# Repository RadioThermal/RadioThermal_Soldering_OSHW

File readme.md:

RadioThermal 470KHz Induction Soldering Station - Open Source Hardware
========================

This repository contains the designs and resources to build a high-performance induction soldering iron at a relatively low cost. [Check out radiothermal.com for more information.](https://radiothermal.com/products.html)

### [Join our Discord server](https://discord.gg/hySrP3z9Kq)

### [Join our mailing list to get updates on this project](https://radiothermal.com/mailing.html)

The 470KHz soldering system is made up of four major components: the power supply, the handpiece, the cable, and the workstand. Follow the links to see the assembly instructions and files for each component.

### [Power Supply](https://github.com/RadioThermal/RadioThermal_Soldering_OSHW/tree/main/Power%20Supply)

The power supply is the core of the 470KHz system. It consists of a PCB design that includes a class-E amplifier and contains impedance matching circuitry to properly provide power to the soldering iron tip. 

### [Handpiece](https://github.com/RadioThermal/RadioThermal_Soldering_OSHW/tree/main/Handpiece)

The handpiece is the primary user interface of the soldering system. It consists of a core built with brass tubing and an outer 3D printed grip for comfort during use.

### [Cable](https://github.com/RadioThermal/RadioThermal_Soldering_OSHW/tree/main/Cable)

The cable is a specially modified RG-174 coaxial cable with SMA connectors on each end. A silicone jacket has been added for burn resistance, with additional silicone layers on each end for improved strain relief

### [Workstand](https://github.com/RadioThermal/RadioThermal_Soldering_OSHW/tree/main/Workstand)

The workstand is a primarly 3D printed part that gives the user a safe place to their hot soldering iron, along with brass wool to clean the tip. Magnets are used to cool down the soldering iron tip when not in use. The back of the stand contains storage for four tips.

### [Extra - Compatibility Adapters](https://github.com/RadioThermal/RadioThermal_Soldering_OSHW/tree/main/Adapters)

We have designed compatibility adapters to allow our cable and handpiece to be used with preexisting 470KHz power supplies including Metcal PS, Metcal MFR, and Thermaltronics TMT-2000.

# Project Status

Here is an overview of the current state of completion for each major component of the project

| Component              | Status                      |
| ---------------------- | --------------------------- |
| Power Supply           | Updated to V2.5B            |
| Handpiece              | Complete                    |
| Cable                  | Complete                    |
| Workstand              | Complete                    |
| Compatibility Adapters | Updated version coming soon |

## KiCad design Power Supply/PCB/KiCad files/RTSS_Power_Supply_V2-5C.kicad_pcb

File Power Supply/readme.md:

# Power Supply

The power supply is the core of the 470KHz system. It is based upon a class-E amplifier and contains impedance matching circuitry to properly provide power to the soldering iron tip.

#### The PCB

The provided PCB design includes all basic functionality needed to operate a 470KHz soldering iron tip. 

The design includes provisions for inrush current limiting, reverse polarity protection, a cooling fan, and two different types of oscillators. The inductors, apart from the fixed 33uH inductor, are all based around the [Kool Mu 0077932A7 core](https://www.mag-inc.com/Media/Magnetics/Datasheets/0077932A7.pdf), which is currently only available from Digikey, though we are looking for alternatives. 

In version 2.5B of the PCB, we have made a few improvements to reduce cost and increase reliability compared with version 2.3B1. Most notably the oscillator section has been redesigned to eliminate the need for a microcontroller and now only relies on a 7.6MHz crystal oscillator and TTL logic. To reduce costs, we have eliminated the daughter board by moving everything onto the main board, additionally L2 has been updated to only use a single inductor core from the two cores required on previous versions. Moving all of this new hardware onto the main board has had the consequence of causing us to remove the TO-247 MOSFET option in favor of TO-220 to save space. 

In the version 2.5C release, the reference designators have been updated on most components to better reflect their placement within the design.

Components required to assemble the board can be found in the [Digikey list we maintain](https://www.digikey.com/en/mylists/list/9TG6QR7M1O) , please let us know if there is a stocking issue for a component so that we can find a suitable alternative.

**Special note:** if you are one of the few people with a **V2.5** non-B PCB, please replace the 74LVC1G14 with a [74LVC2G14](https://www.digikey.com/en/products/detail/evvo/SN74LVC2G14DBVR-EV/22674516) and ensure the [74LVC1GU04](https://www.digikey.com/en/products/detail/texas-instruments/SN74LVC1GU04DBVR/377459) is a SOT23-5 package

#### External DC Power Supplies

For testing we have been using Chicony A15-180P1A 20V 180W power supplies, however any power supply in the 18-24V range with a 100W or higher rating will work. We recommend utilizing a laptop power supply since they can be found on the used market at reasonable prices. Alternatively, a USB-C PD trigger board can be used in conjunction with a USB PD power supply that supports 20V 5A output.

#### The Case

The case design adds additional functionality to the PCB including a barrel jack for power input, a convenient power switch, power indicator LED, cooling fan, and a ground connection point. The airflow paths of the case have been optimized to exhaust out the front and back with the intake on top, keeping all of the inductors cool.

The electronics parts and fasteners for the case [can be purchased from Digikey](https://www.digikey.com/en/mylists/list/JW0L0CD7FY). 

The case fan mounts are only designed to support Delta AFB0712 series fans at present, other 70mm fans can be used by removing the fan mounting posts and gluing the four corners of the fan in place.

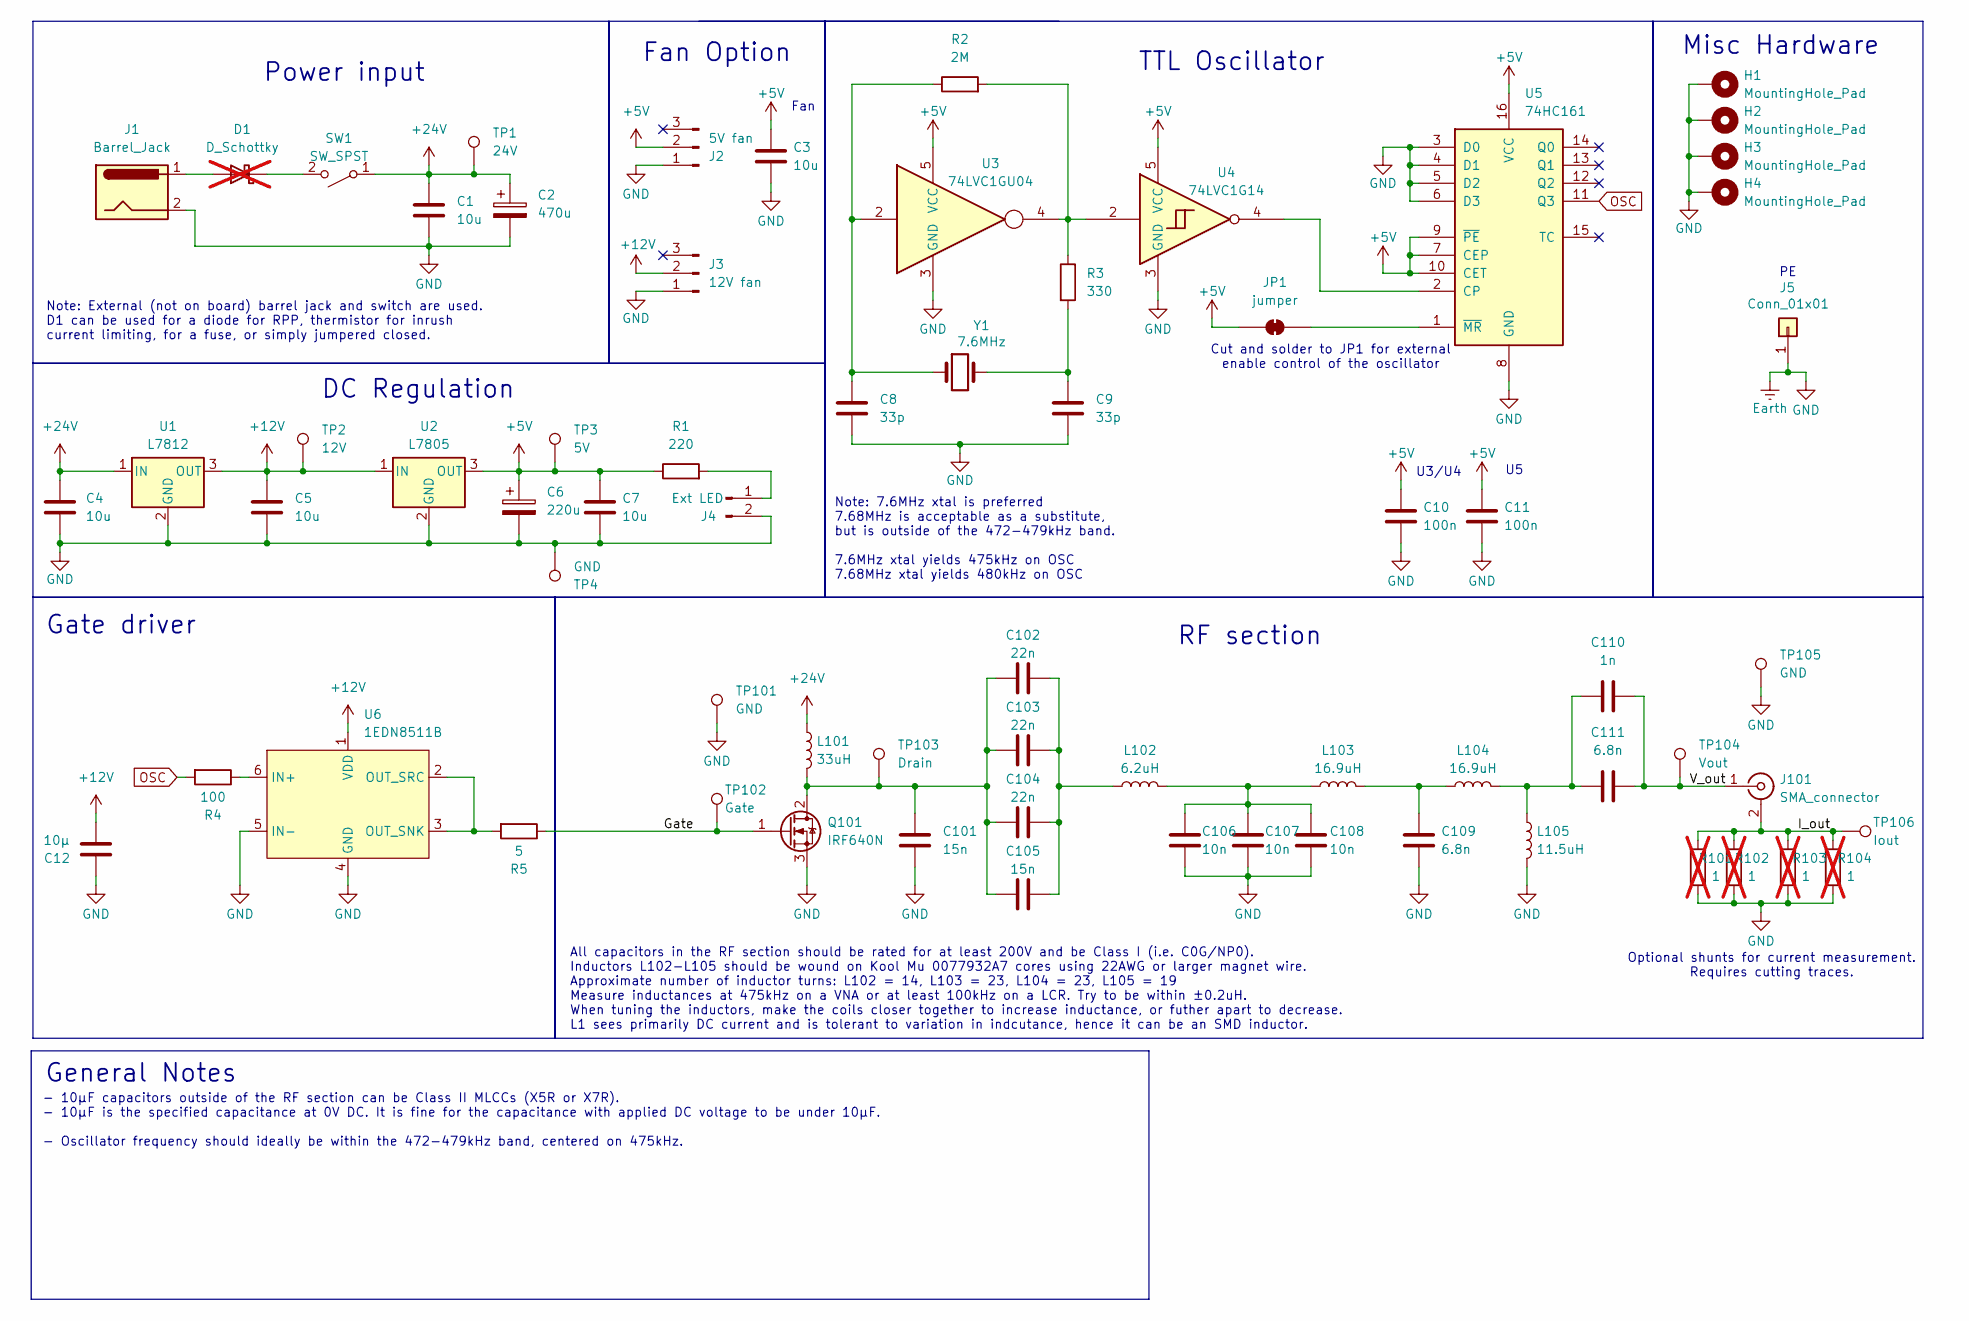
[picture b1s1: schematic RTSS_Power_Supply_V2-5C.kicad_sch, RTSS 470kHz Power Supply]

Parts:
C1, C3, C4, C5, C7: 10u; C_1206_3216Metric_Pad1.33x1.80mm_HandSolder
C2: 470u; CP_Radial_D10.0mm_P5.00mm_P7.50mm
C6: 220u; CP_Radial_D6.3mm_P2.50mm
C8, C9: 33p; C_0603_1608Metric
C10, C11: 100n; C_0603_1608Metric
C12: 10µ; C_1206_3216Metric_Pad1.33x1.80mm_HandSolder
C101, C105: 15n; C_1210_3225Metric_Pad1.33x2.70mm_HandSolder
C102, C103, C104: 22n; C_1206_3216Metric_Pad1.33x1.80mm_HandSolder
C106, C107, C108: 10n; C_1206_3216Metric_Pad1.33x1.80mm_HandSolder
C109, C111: 6.8n; C_1210_3225Metric_Pad1.33x2.70mm_HandSolder
C110: 1n; C_1206_3216Metric_Pad1.33x1.80mm_HandSolder
D1: D_Schottky; TO-220-2_Vertical; not fitted
H1, H2, H3, H4: MountingHole_Pad; MountingHole_3.2mm_M3_DIN965_Pad
J1: Barrel_Jack; 3D-JWT_A3963_1x02_P3.96mm_Vertical
J2: 5V fan; FanPinHeader_1x03_P2.54mm_Vertical
J3: 12V fan; FanPinHeader_1x03_P2.54mm_Vertical
J4: Ext LED; PinHeader_1x02_P2.54mm_Vertical
J5: Conn_01x01; SolderWire-1sqmm_1x01_D1.4mm_OD2.7mm
J101: SMA_connector; SMA_EdgeMount_Horizontal
JP1: jumper; SolderJumper-2_P1.3mm_Bridged_RoundedPad1.0x1.5mm
L101: 33uH; L_Pulse_PA4343
L102: 6.2uH; L_Koolmu_1x_small_THTonly_0077932A7
L103, L104: 16.9uH; L_Koolmu_1x_small_THTonly_0077932A7
L105: 11.5uH; L_Koolmu_1x_small_THTonly_0077932A7
Q101: IRF640N; 3D_TO-220-3_Vertical
R1: 220; C_0805_2012Metric_Pad1.18x1.45mm_HandSolder
R2: 2M; R_0805_2012Metric
R3: 330; R_0805_2012Metric
R4: 100; R_0805_2012Metric
R5: 5; Bridge_R_0805_2012Metric
R101, R102, R103, R104: 1; Bridge_R_1206_3216Metric; not fitted
SW1: SW_SPST; 3D-JWT_A3963_1x02_P3.96mm_Vertical
TP1: 24V; TestPoint_Plated_Hole_D2.0mm
TP2: 12V; TestPoint_Pad_D1.0mm
TP3: 5V; TestPoint_Pad_D1.0mm
TP4: GND; TestPoint_Pad_D1.0mm
TP101, TP105: GND; TestPoint_THTPad_2.0x2.0mm_Drill1.0mm
TP102: Gate; TestPoint_THTPad_2.0x2.0mm_Drill1.0mm
TP103: Drain; TestPoint_THTPad_2.0x2.0mm_Drill1.0mm
TP104: Vout; TestPoint_THTPad_2.0x2.0mm_Drill1.0mm
TP106: Iout; TestPoint_THTPad_2.0x2.0mm_Drill1.0mm
U1: L7812; TO-252-3_TabPin2
U2: L7805; TO-252-3_TabPin2
U3: 74LVC1GU04; SOT-553
U4: 74LVC1G14; SOT-553
U5: 74HC161; SOP-16_4.4x10.4mm_P1.27mm
U6: 1EDN8511B; SOT-23-6_Handsoldering
Y1: 7.6MHz; Crystal_SMD_HC49-SD

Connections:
+5V: C3.1, C6.1, C7.1, C10.1, C11.1, J2.2, JP1.1 (A), R1.1, TP3.1 (1_1), U2.3 (OUT), U3.5 (VCC), U4.5 (VCC), U5.7 (CEP), U5.9 (~PE), U5.10 (CET), U5.16 (VCC)
+12V: C5.1, C12.2, J3.2, TP2.1 (1_1), U1.3 (OUT), U2.1 (IN), U6.1 (VDD)
+24V: C1.1, C2.1, C4.1, L101.1, SW1.1 (A), TP1.1 (1_1), U1.1 (IN)
/Gate: Q101.1 (G), R5.1, TP102.1 (1_1)
/I_out: J101.2 (Ext), R101.1, R102.1, R103.1, R104.1, TP106.1 (1_1)
/V_out: C110.2, C111.2, J101.1 (In), TP104.1 (1_1)
Earth: C1.2, C2.2, C3.2, C4.2, C5.2, C6.2, C7.2, C8.2, C9.2, C10.2, C11.2, C12.1, C101.2, C106.2, C107.2, C108.2, C109.2, H1.1 (1_1), H2.1 (1_1), H3.1 (1_1), H4.1 (1_1), J1.2, J2.1, J3.1, J4.2, J5.1 (Pin_1_1), L105.2, Q101.3 (S), R101.2, R102.2, R103.2, R104.2, TP4.1 (1_1), TP101.1 (1_1), TP105.1 (1_1), U1.2 (GND), U2.2 (GND), U3.3 (GND), U4.3 (GND), U5.3 (D0), U5.4 (D1), U5.5 (D2), U5.6 (D3), U5.8 (GND), U6.4 (GND), U6.5 (IN-)
unnamed: C8.1, R2.1, U3.2, Y1.1
unnamed: C9.1, R3.2, Y1.2
unnamed: C102.2, C103.2, C104.2, C105.2, L102.1
unnamed: C106.1, C107.1, C108.1, L102.2, L103.1
unnamed: C109.1, L103.2, L104.1
unnamed: C110.1, C111.1, L104.2, L105.1
unnamed: D1.2 (A), J1.1
unnamed: D1.1 (K), SW1.2 (B)
unnamed: J4.1, R1.2
unnamed: JP1.2 (B), U5.1 (~MR)
unnamed: C101.1, C102.1, C103.1, C104.1, C105.1, L101.2, Q101.2 (D), TP103.1 (1_1)
unnamed: R2.2, R3.1, U3.4, U4.2
unnamed: U4.4, U5.2 (CP)
unnamed: R4.1, U6.6 (IN+)
unnamed: R5.2, U6.2 (OUT_SRC), U6.3 (OUT_SNK)
OSC: R4.2, U5.11 (Q3)

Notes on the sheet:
RF section
Note: 7.6MHz xtal is preferred 7.68MHz is acceptable as a substitute, but is outside of the 472-479kHz band. 7.6MHz xtal yields 475kHz on OSC 7.68MHz xtal yields 480kHz on OSC
Cut and solder to JP1 for external enable control of the oscillator
Gate driver
All capacitors in the RF section should be rated for at least 200V and be Class I (i.e. C0G/NP0). Inductors L102-L105 should be wound on Kool Mu 0077932A7 cores using 22AWG or larger magnet wire. Approximate number of inductor turns: L102 = 14, L103 = 23, L104 = 23, L105 = 19 Measure inductances at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
Power input
Misc Hardware
TTL Oscillator
Fan Option
U3/U4
General Notes
Note: External (not on board) barrel jack and switch are used. D1 can be used for a diode for RPP, thermistor for inrush current limiting, for a fuse, or simply jumpered closed.
- 10µF capacitors outside of the RF section can be Class II MLCCs (X5R or X7R). - 10µF is the specified capacitance at 0V DC. It is fine for the capacitance with applied DC voltage to be under 10µF. - Oscillator frequency should ideally be within the 472-479kHz band, centered on 475kHz.
Optional shunts for current measurement. Requires cutting traces.
Fan
DC Regulation

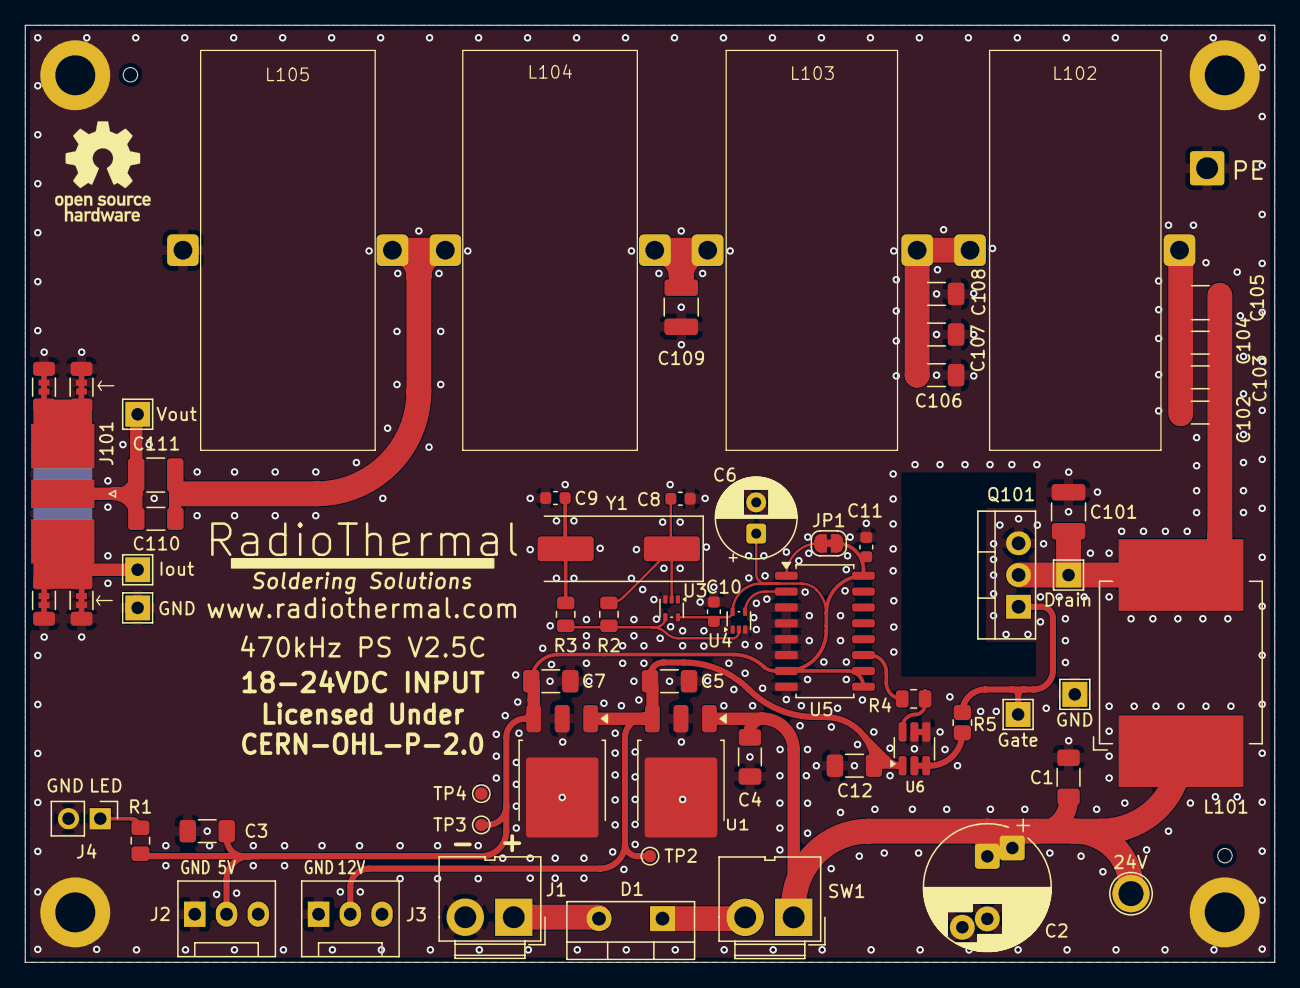
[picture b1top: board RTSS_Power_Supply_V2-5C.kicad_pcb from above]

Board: 2 copper layers, 100.0 x 75.0 mm, 68 parts (0 on the bottom side), 23 nets.

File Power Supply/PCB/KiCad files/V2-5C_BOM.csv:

"Reference","Qty","Value","DNP","Exclude from BOM","Exclude from Board","Footprint","Datasheet"
"C1,C3,C4,C5,C7","5","10u","","","","Capacitor_SMD:C_1206_3216Metric_Pad1.33x1.80mm_HandSolder",""
"C2","1","470u","","","","Capacitor_THT:CP_Radial_D10.0mm_P5.00mm_P7.50mm",""
"C6","1","220u","","","","Capacitor_THT:CP_Radial_D6.3mm_P2.50mm",""
"C8,C9","2","33p","","","","Capacitor_SMD:C_0603_1608Metric",""
"C10,C11","2","100n","","","","Capacitor_SMD:C_0603_1608Metric",""
"C12","1","10µ","","","","Capacitor_SMD:C_1206_3216Metric_Pad1.33x1.80mm_HandSolder",""
"C101,C105","2","15n","","","","Capacitor_SMD:C_1210_3225Metric_Pad1.33x2.70mm_HandSolder",""
"C102,C103,C104","3","22n","","","","Capacitor_SMD:C_1206_3216Metric_Pad1.33x1.80mm_HandSolder",""
"C106,C107,C108","3","10n","","","","Capacitor_SMD:C_1206_3216Metric_Pad1.33x1.80mm_HandSolder",""
"C109,C111","2","6.8n","","","","Capacitor_SMD:C_1210_3225Metric_Pad1.33x2.70mm_HandSolder",""
"C110","1","1n","","","","Capacitor_SMD:C_1206_3216Metric_Pad1.33x1.80mm_HandSolder",""
"J1","1","Barrel_Jack","","","","custom_parts:3D-JWT_A3963_1x02_P3.96mm_Vertical",""
"J2","1","5V fan","","","","Connector:FanPinHeader_1x03_P2.54mm_Vertical",""
"J3","1","12V fan","","","","Connector:FanPinHeader_1x03_P2.54mm_Vertical",""
"J4","1","Ext LED","","","","Connector_PinHeader_2.54mm:PinHeader_1x02_P2.54mm_Vertical",""
"J101","1","SMA_connector","","","","custom_parts:SMA_EdgeMount_Horizontal",""
"L101","1","33uH","","","","custom_parts:L_Pulse_PA4343",""
"L102","1","6.2uH","","","","custom_parts:L_Koolmu_1x_small_THTonly_0077932A7",""
"L103,L104","2","16.9uH","","","","custom_parts:L_Koolmu_1x_small_THTonly_0077932A7",""
"L105","1","11.5uH","","","","custom_parts:L_Koolmu_1x_small_THTonly_0077932A7",""
"Q101","1","IRF640N","","","","custom_parts:3D_TO-220-3_Vertical","https://www.infineon.com/assets/row/public/documents/24/49/i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"
"R1","1","220","","","","Capacitor_SMD:C_0805_2012Metric_Pad1.18x1.45mm_HandSolder",""
"R2","1","2M","","","","Resistor_SMD:R_0805_2012Metric",""
"R3","1","330","","","","Resistor_SMD:R_0805_2012Metric",""
"R4","1","100","","","","Resistor_SMD:R_0805_2012Metric",""
"R5","1","5","","","","custom_parts:Bridge_R_0805_2012Metric",""
"SW1","1","SW_SPST","","","","custom_parts:3D-JWT_A3963_1x02_P3.96mm_Vertical",""
"TP1","1","24V","","","","TestPoint:TestPoint_Plated_Hole_D2.0mm",""
"TP2","1","12V","","","","TestPoint:TestPoint_Pad_D1.0mm",""
"TP3","1","5V","","","","TestPoint:TestPoint_Pad_D1.0mm",""
"TP4","1","GND","","","","TestPoint:TestPoint_Pad_D1.0mm",""
"TP101,TP105","2","GND","","","","TestPoint:TestPoint_THTPad_2.0x2.0mm_Drill1.0mm",""
"TP102","1","Gate","","","","TestPoint:TestPoint_THTPad_2.0x2.0mm_Drill1.0mm",""
"TP103","1","Drain","","","","TestPoint:TestPoint_THTPad_2.0x2.0mm_Drill1.0mm",""
"TP104","1","Vout","","","","TestPoint:TestPoint_THTPad_2.0x2.0mm_Drill1.0mm",""
"TP106","1","Iout","","","","TestPoint:TestPoint_THTPad_2.0x2.0mm_Drill1.0mm",""
"U1","1","L7812","","","","Package_TO_SOT_SMD:TO-252-3_TabPin2","http://www.st.com/content/ccc/resource/technical/document/da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"
"U2","1","L7805","","","","Package_TO_SOT_SMD:TO-252-3_TabPin2","http://www.st.com/content/ccc/resource/technical/document/da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"
"U3","1","74LVC1GU04","","","","Package_TO_SOT_SMD:SOT-553","http://www.ti.com/lit/ds/symlink/sn74lvc1gu04.pdf"
"U4","1","74LVC1G14","","","","Package_TO_SOT_SMD:SOT-553","https://www.ti.com/lit/ds/symlink/sn74lvc1g14.pdf"
"U5","1","74HC161","","","","Package_SO:SOP-16_4.4x10.4mm_P1.27mm","http://www.ti.com/lit/gpn/sn74LS161"
"U6","1","1EDN8511B","","","","Package_TO_SOT_SMD:SOT-23-6_Handsoldering",""
"Y1","1","7.6MHz","","","","Crystal:Crystal_SMD_HC49-SD",""

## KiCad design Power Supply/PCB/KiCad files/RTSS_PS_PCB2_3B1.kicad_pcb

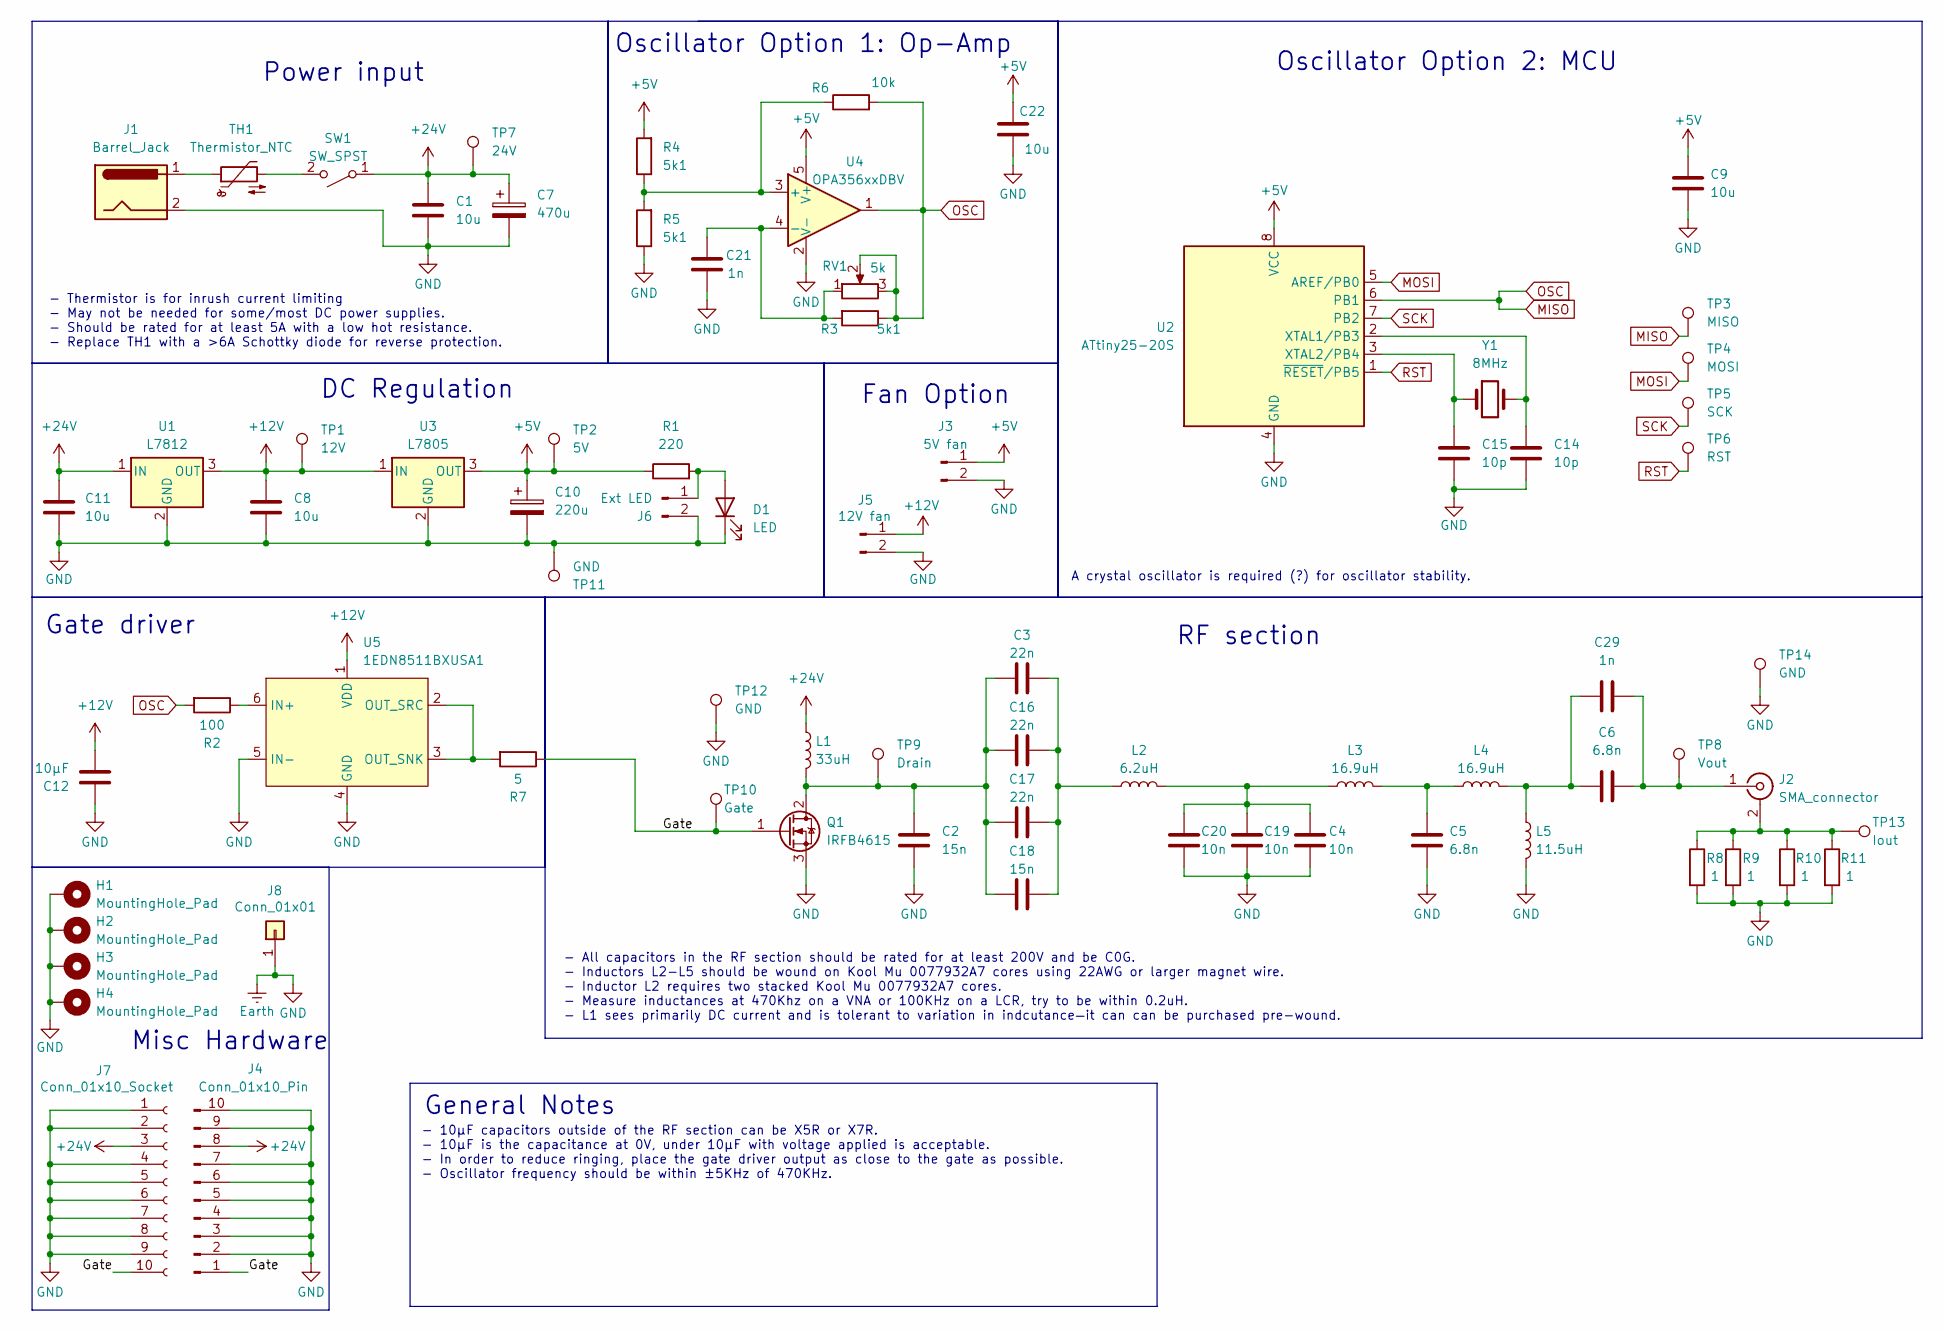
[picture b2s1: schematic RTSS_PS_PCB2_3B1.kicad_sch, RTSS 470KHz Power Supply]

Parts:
C1, C8, C9, C11, C22: 10u; C_1206_3216Metric_Pad1.33x1.80mm_HandSolder
C2, C18: 15n; C_1206_3216Metric_Pad1.33x1.80mm_HandSolder
C3, C16, C17: 22n; C_1206_3216Metric_Pad1.33x1.80mm_HandSolder
C4, C19, C20: 10n; C_1206_3216Metric_Pad1.33x1.80mm_HandSolder
C5, C6: 6.8n; C_1206_3216Metric_Pad1.33x1.80mm_HandSolder
C7: 470u; CP_Radial_D10.0mm_P5.00mm_P7.50mm
C10: 220u; CP_Radial_D6.3mm_P2.50mm
C12: 10µF; C_1206_3216Metric_Pad1.33x1.80mm_HandSolder
C14, C15: 10p; C_0805_2012Metric
C21: 1n; C_0805_2012Metric
C29: 1n; C_1206_3216Metric_Pad1.33x1.80mm_HandSolder
D1: LED; LED_1206_3216Metric_Pad1.42x1.75mm_HandSolder
H1, H2, H3, H4: MountingHole_Pad; MountingHole_3.2mm_M3_DIN965_Pad
J1: Barrel_Jack; JWT_A3963_1x02_P3.96mm_Vertical
J2: SMA_connector; SMA_EdgeMount_Horizontal
J3: 5V fan; PinHeader_1x02_P2.54mm_Vertical
J4: Conn_01x10_Pin; PinHeader_1x10_P2.54mm_Horizontal
J5: 12V fan; PinHeader_1x02_P2.54mm_Vertical
J6: Ext LED; PinHeader_1x02_P2.54mm_Vertical
J7: Conn_01x10_Socket; PinSocket_1x10_P2.54mm_Vertical
J8: Conn_01x01; SolderWire-1sqmm_1x01_D1.4mm_OD2.7mm
L1: 33uH; L_Pulse_PA4343
L2: 6.2uH; V2_L_Koolmu_2x_small_THT_0077932A7_1
L3, L4: 16.9uH; V2_L_Koolmu_1x_small_THT_0077932A7_1
L5: 11.5uH; V2_L_Koolmu_1x_small_THT_0077932A7_1
Q1: IRFB4615; TO-247_220_Vertical
R1: 220; R_1206_3216Metric_Pad1.30x1.75mm_HandSolder
R2: 100; R_0805_2012Metric
R3: 5k; R_0805_2012Metric
R4, R5: 5k1; R_0805_2012Metric
R6: 10k; R_0805_2012Metric
R7: 5; R_0805_2012Metric
R8, R9, R10, R11: 1; R_1206_3216Metric
RV1: 5k1; Potentiometer_Bourns_TC33X_Vertical
SW1: SW_SPST; JWT_A3963_1x02_P3.96mm_Vertical
TH1: Thermistor_NTC; C_Disc_D11.0mm_W5.0mm_P5.00mm
TP1: 12V; TestPoint_Pad_D1.0mm
TP2: 5V; TestPoint_Pad_D1.0mm
TP3: MISO; TestPoint_Pad_D1.0mm
TP4: MOSI; TestPoint_Pad_D1.0mm
TP5: SCK; TestPoint_Pad_D1.0mm
TP6: RST; TestPoint_Pad_D1.0mm
TP7: 24V; TestPoint_Plated_Hole_D2.0mm
TP8: Vout; TestPoint_THTPad_2.0x2.0mm_Drill1.0mm
TP9: Drain; TestPoint_THTPad_2.0x2.0mm_Drill1.0mm
TP10: Gate; TestPoint_THTPad_2.0x2.0mm_Drill1.0mm
TP11: GND; TestPoint_Pad_D1.0mm
TP12, TP14: GND; TestPoint_THTPad_2.0x2.0mm_Drill1.0mm
TP13: Iout; TestPoint_THTPad_2.0x2.0mm_Drill1.0mm
U1: L7812; TO-252-3_TabPin2
U2: ATtiny25-20S; SOIC-8_5.3x5.3mm_P1.27mm
U3: L7805; TO-252-3_TabPin2
U4: OPA356xxDBV; SOT-23-5
U5: 1EDN8511BXUSA1; SOT-23-6_Handsoldering
Y1: 8MHz; Crystal_SMD_HC49-SD

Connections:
+5V: C9.1, C10.1, C22.1, J3.1, R1.1, R4.2, TP2.1, U2.8 (VCC), U3.3 (OUT), U4.5 (V+)
+12V: C8.1, C12.2, J5.1, TP1.1, U1.3 (OUT), U3.1 (IN), U5.1 (VDD)
+24V: C1.1, C7.1, C11.1, J4.8, J7.3, L1.1, SW1.1 (A), TP7.1, U1.1 (IN)
/Gate: J4.1, J7.10, Q1.1 (G), R7.1, TP10.1
Earth: C1.2, C2.2, C4.2, C5.2, C7.2, C8.2, C9.2, C10.2, C11.2, C12.1, C14.2, C15.2, C19.2, C20.2, C21.1, C22.2, D1.1 (K), H1.1, H2.1, H3.1, H4.1, J1.2, J3.2, J4.2, J4.3, J4.4, J4.5, J4.6, J4.7, J4.9, J4.10, J5.2, J6.2, J7.1, J7.2, J7.4, J7.5, J7.6, J7.7, J7.8, J7.9, J8.1, L5.2, Q1.3 (S), R5.1, R8.2, R9.2, R10.2, R11.2, TP11.1, TP12.1, TP14.1, U1.2 (GND), U2.4 (GND), U3.2 (GND), U4.2 (V-), U5.4 (GND), U5.5 (IN-)
MISO: R2.2, R3.1, R6.2, RV1.2, RV1.3, TP3.1, U2.6 (PB1), U4.1
MOSI: TP4.1, U2.5 (AREF/PB0)
unnamed: C5.1, L3.2, L4.1
unnamed: C3.2, C16.2, C17.2, C18.2, L2.1
unnamed: C4.1, C19.1, C20.1, L2.2, L3.1
unnamed: C6.1, C29.1, L4.2, L5.1
unnamed: D1.2 (A), J6.1, R1.2
unnamed: J1.1, TH1.1
unnamed: J2.2 (Ext), R8.1, R9.1, R10.1, R11.1, TP13.1
unnamed: C6.2, C29.2, J2.1 (In), TP8.1
unnamed: C2.1, C3.1, C16.1, C17.1, C18.1, L1.2, Q1.2 (D), TP9.1
unnamed: SW1.2 (B), TH1.2
unnamed: C14.1, U2.2 (XTAL1/PB3), Y1.2
unnamed: C15.1, U2.3 (XTAL2/PB4), Y1.1
unnamed: R4.1, R5.2, R6.1, U4.3 (+)
unnamed: C21.2, R3.2, RV1.1, U4.4 (-)
unnamed: R2.1, U5.6 (IN+)
unnamed: R7.2, U5.2 (OUT_SRC), U5.3 (OUT_SNK)
RST: TP6.1, U2.1 (~RESET/PB5)
SCK: TP5.1, U2.7 (PB2)

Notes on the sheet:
RF section
A crystal oscillator is required (?) for oscillator stability.
Misc Hardware
Gate driver
- All capacitors in the RF section should be rated for at least 200V and be C0G. - Inductors L2-L5 should be wound on Kool Mu 0077932A7 cores using 22AWG or larger magnet wire. - Inductor L2 requires two stacked Kool Mu 0077932A7 cores. - Measure inductances at 470Khz on a VNA or 100KHz on a LCR, t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
Power input
Oscillator Option 2: MCU
Oscillator Option 1: Op-Amp
General Notes
Fan Option
- Thermistor is for inrush current limiting - May not be needed for some/most DC power supplies. - Should be rated for at least 5A with a low hot resistance. - Replace TH1 with a >6A Schottky diode for reverse protection.
- 10µF capacitors outside of the RF section can be X5R or X7R. - 10µF is the capacitance at 0V, under 10µF with voltage applied is acceptable. - In order to reduce ringing, place the gate driver output as close to the gate as possible. - Oscillator frequency should be within ±5KHz of 470KHz.
DC Regulation

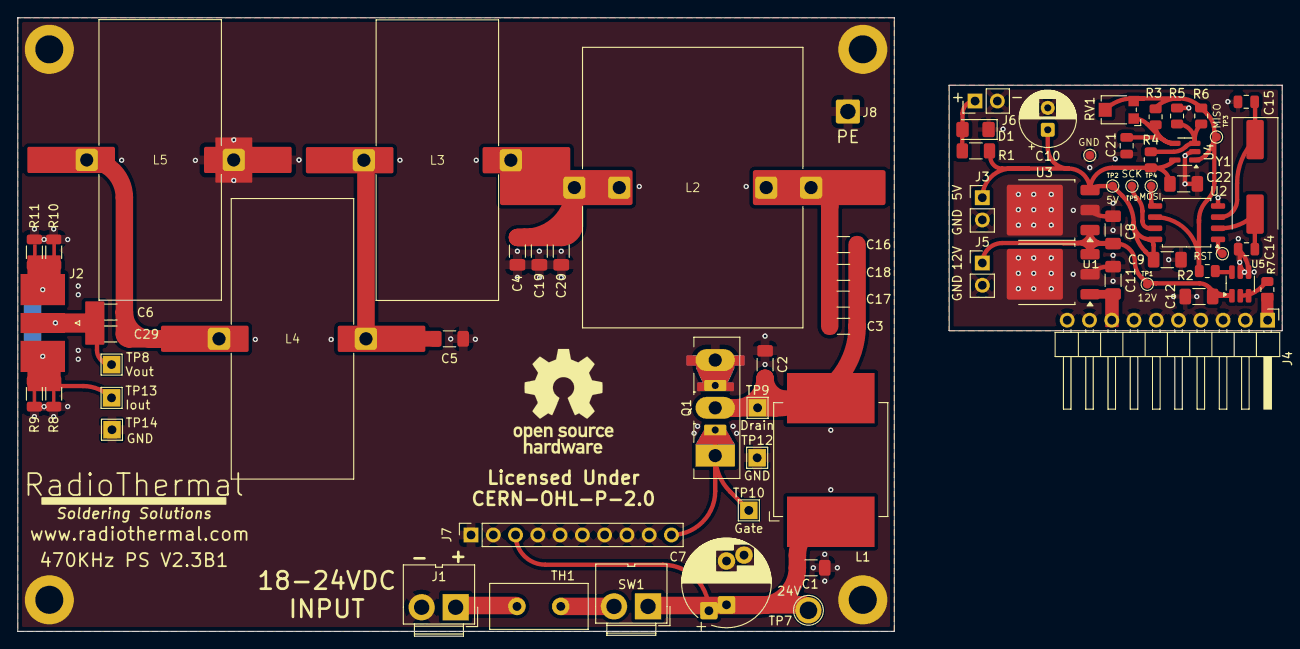
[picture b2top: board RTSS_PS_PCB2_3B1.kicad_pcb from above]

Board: 2 copper layers, 144.2 x 70.0 mm, 75 parts (0 on the bottom side), 25 nets.

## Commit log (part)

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2025-07-18 Uploaded initial release files
2025-07-18 added initial release files
2025-07-18 Update LICENSE.md to permissive variant
2025-07-18 Update readme.md with correct folder links
2025-07-18 Update readme.md with proper links
2025-07-18 added mailing list link
2025-07-21 Fix typo in mailing list in readme.md
2026-03-16 Added PCB design and adapter schematic
2026-03-16 updated readme for Power Supplyt
2026-03-29 Updated workstand design and added photos
2026-03-29 Update readme.md
    Fixed error with heading
2026-04-04 Added power supply case design
    workstand instructions added and DIN adapter image fixed

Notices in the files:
Power Supply/PCB/KiCad files/RTSS_PS_PCB2_3B1.kicad_pcb:
Licensed Under
CERN-OHL-P-2.0
